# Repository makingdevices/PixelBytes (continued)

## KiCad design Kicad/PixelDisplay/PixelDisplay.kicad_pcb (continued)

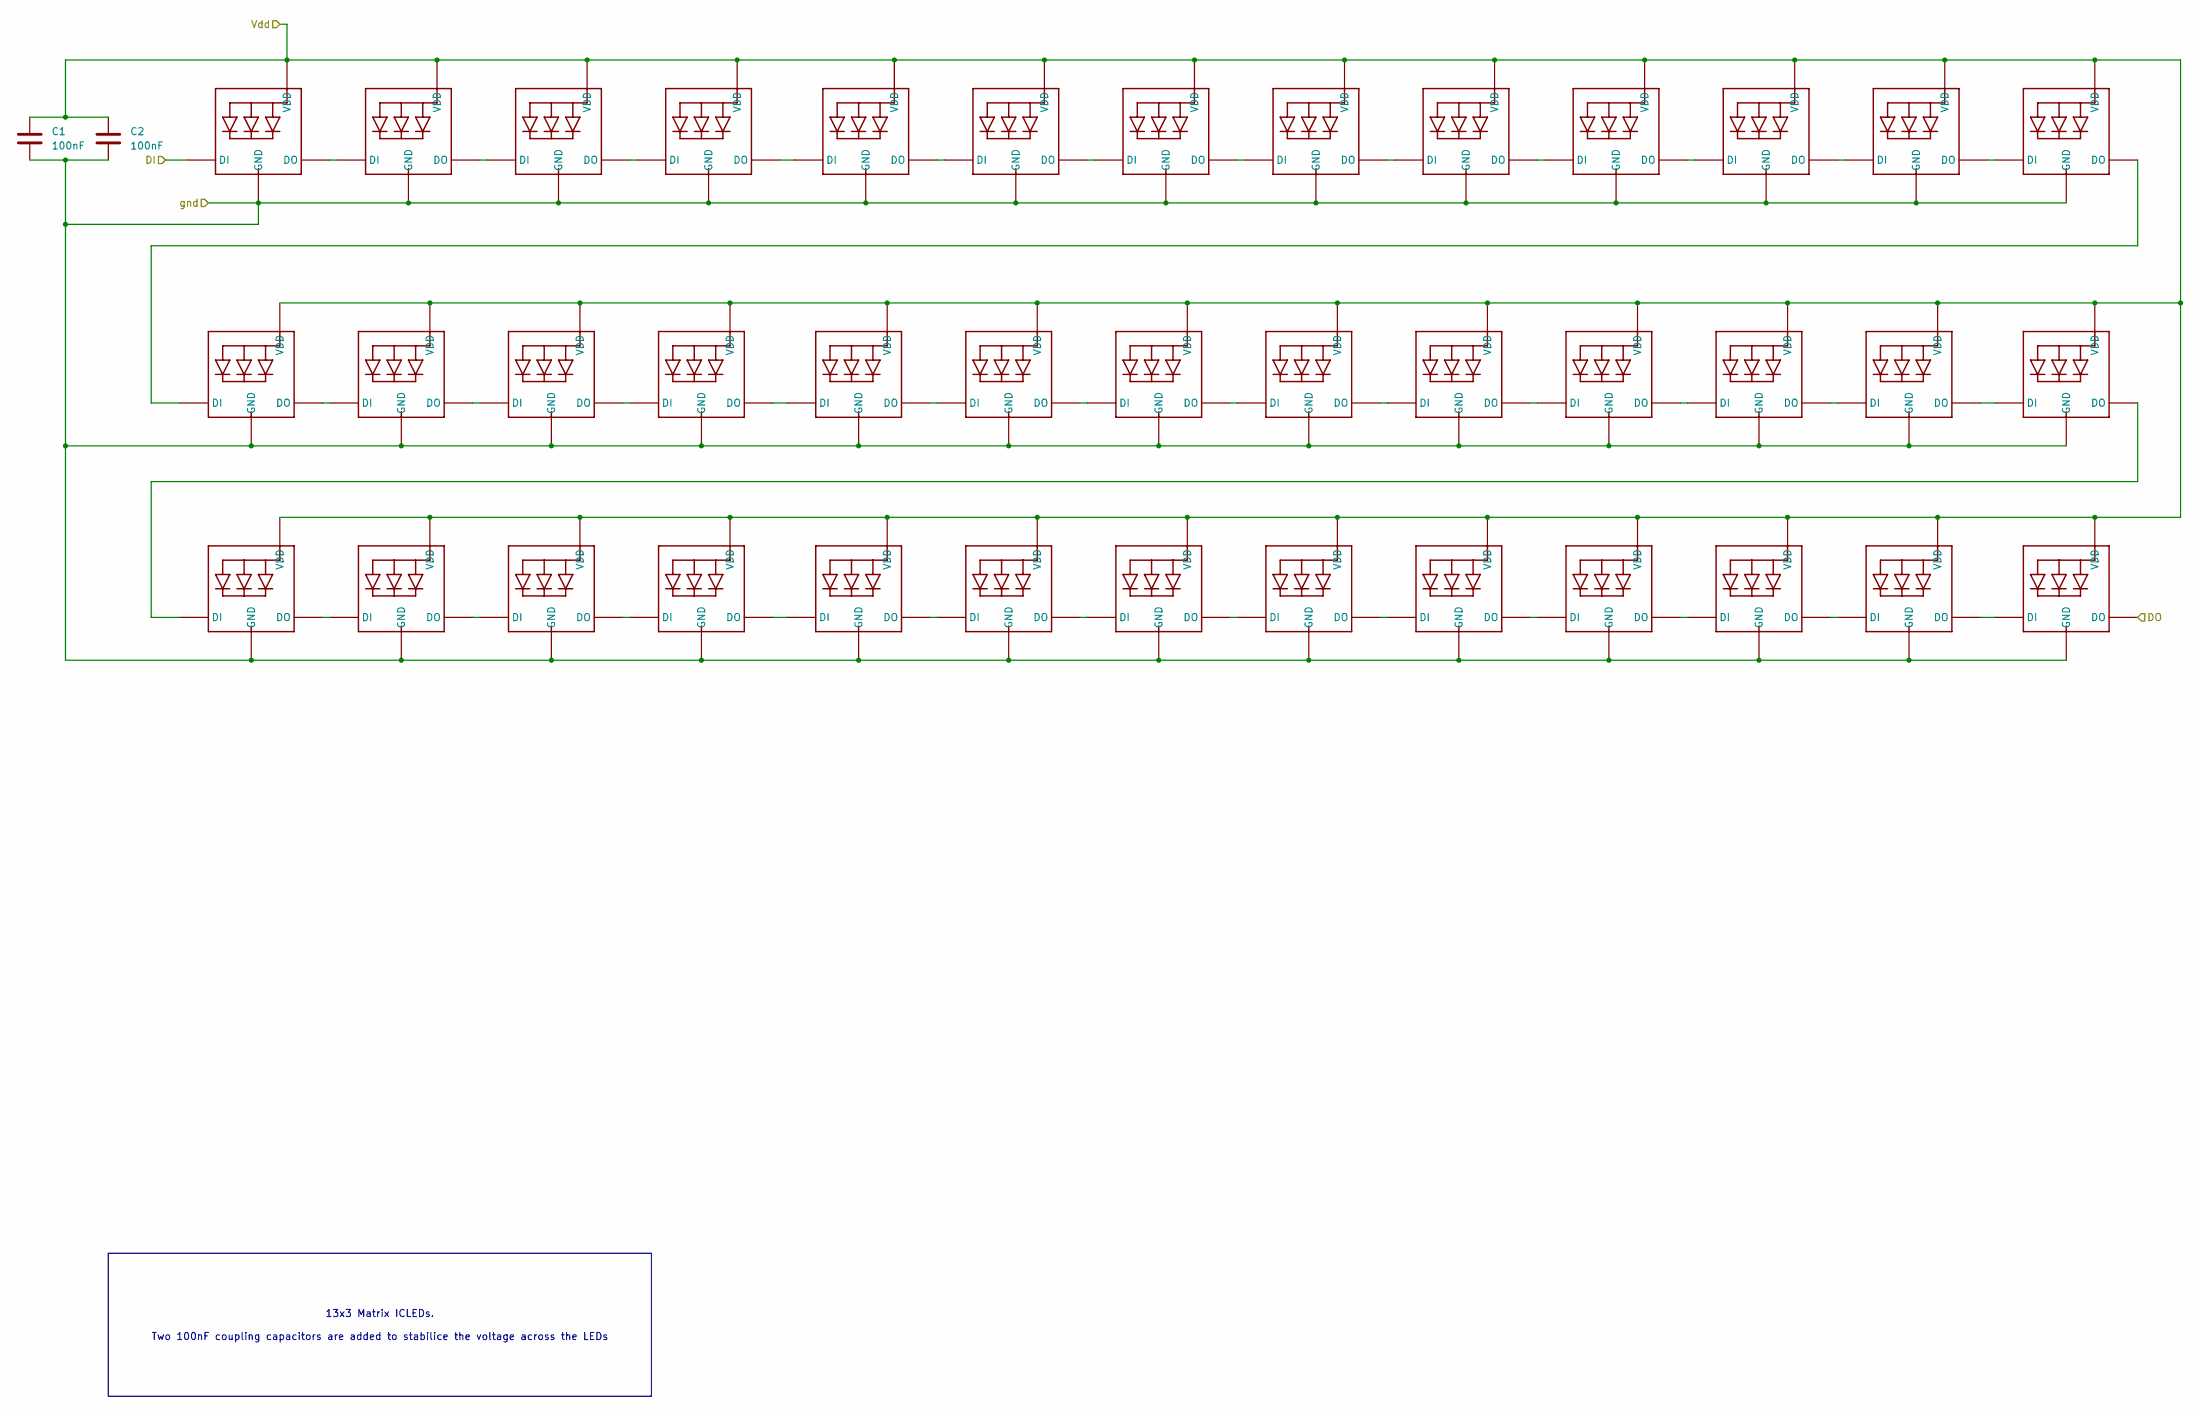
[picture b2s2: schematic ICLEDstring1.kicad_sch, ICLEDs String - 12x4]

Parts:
C1, C2: 100nF; C_0805_2012Metric
ICled1, ICled2, ICled3, ICled4, ICled5, ICled6, ICled7, ICled8, ICled9, ICled10, ICled11, ICled12, ICled13, ICled14, ICled15, ICled16, ICled17, ICled18, ICled19, ICled20, ICled21, ICled22, ICled23, ICled24, ICled25, ICled26, ICled27, ICled28, ICled29, ICled30, ICled31, ICled32, ICled33, ICled34, ICled35, ICled36, ICled37, ICled38, ICled39: 1312020030000

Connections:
unnamed: ICled1.3-DIN (DI), ICled37.1-DOUT (DO)
unnamed: ICled1.1-DOUT (DO), ICled4.3-DIN (DI)
unnamed: ICled2.3-DIN (DI), ICled38.1-DOUT (DO)
unnamed: ICled2.1-DOUT (DO), ICled5.3-DIN (DI)
unnamed: ICled3.1-DOUT (DO), ICled6.3-DIN (DI)
unnamed: ICled4.1-DOUT (DO), ICled7.3-DIN (DI)
unnamed: ICled5.1-DOUT (DO), ICled8.3-DIN (DI)
unnamed: ICled6.1-DOUT (DO), ICled9.3-DIN (DI)
unnamed: ICled7.1-DOUT (DO), ICled10.3-DIN (DI)
unnamed: ICled10.1-DOUT (DO), ICled13.3-DIN (DI)
unnamed: ICled8.1-DOUT (DO), ICled11.3-DIN (DI)
unnamed: ICled11.1-DOUT (DO), ICled14.3-DIN (DI)
unnamed: ICled9.1-DOUT (DO), ICled12.3-DIN (DI)
unnamed: ICled12.1-DOUT (DO), ICled15.3-DIN (DI)
unnamed: ICled13.1-DOUT (DO), ICled16.3-DIN (DI)
unnamed: ICled14.1-DOUT (DO), ICled17.3-DIN (DI)
unnamed: ICled15.1-DOUT (DO), ICled18.3-DIN (DI)
unnamed: ICled16.1-DOUT (DO), ICled19.3-DIN (DI)
unnamed: ICled17.1-DOUT (DO), ICled20.3-DIN (DI)
unnamed: ICled18.1-DOUT (DO), ICled21.3-DIN (DI)
unnamed: ICled19.1-DOUT (DO), ICled22.3-DIN (DI)
unnamed: ICled20.1-DOUT (DO), ICled23.3-DIN (DI)
unnamed: ICled21.1-DOUT (DO), ICled24.3-DIN (DI)
unnamed: ICled22.1-DOUT (DO), ICled25.3-DIN (DI)
unnamed: ICled23.1-DOUT (DO), ICled26.3-DIN (DI)
unnamed: ICled24.1-DOUT (DO), ICled27.3-DIN (DI)
unnamed: ICled25.1-DOUT (DO), ICled28.3-DIN (DI)
unnamed: ICled26.1-DOUT (DO), ICled29.3-DIN (DI)
unnamed: ICled27.1-DOUT (DO), ICled30.3-DIN (DI)
unnamed: ICled28.1-DOUT (DO), ICled31.3-DIN (DI)
unnamed: ICled29.1-DOUT (DO), ICled32.3-DIN (DI)
unnamed: ICled30.1-DOUT (DO), ICled33.3-DIN (DI)
unnamed: ICled31.1-DOUT (DO), ICled34.3-DIN (DI)
unnamed: ICled32.1-DOUT (DO), ICled35.3-DIN (DI)
unnamed: ICled33.1-DOUT (DO), ICled36.3-DIN (DI)
unnamed: ICled34.1-DOUT (DO), ICled38.3-DIN (DI)
unnamed: ICled35.1-DOUT (DO), ICled39.3-DIN (DI)
unnamed: ICled36.1-DOUT (DO), ICled37.3-DIN (DI)
Vdd_str1: C1.1, C2.1, ICled1.2-VDD (VDD), ICled2.2-VDD (VDD), ICled3.2-VDD (VDD), ICled4.2-VDD (VDD), ICled5.2-VDD (VDD), ICled6.2-VDD (VDD), ICled7.2-VDD (VDD), ICled8.2-VDD (VDD), ICled9.2-VDD (VDD), ICled10.2-VDD (VDD), ICled11.2-VDD (VDD), ICled12.2-VDD (VDD), ICled13.2-VDD (VDD), ICled14.2-VDD (VDD), ICled15.2-VDD (VDD), ICled16.2-VDD (VDD), ICled17.2-VDD (VDD), ICled18.2-VDD (VDD), ICled19.2-VDD (VDD), ICled20.2-VDD (VDD), ICled21.2-VDD (VDD), ICled22.2-VDD (VDD), ICled23.2-VDD (VDD), ICled24.2-VDD (VDD), ICled25.2-VDD (VDD), ICled26.2-VDD (VDD), ICled27.2-VDD (VDD), ICled28.2-VDD (VDD), ICled29.2-VDD (VDD), ICled30.2-VDD (VDD), ICled31.2-VDD (VDD), ICled32.2-VDD (VDD), ICled33.2-VDD (VDD), ICled34.2-VDD (VDD), ICled35.2-VDD (VDD), ICled36.2-VDD (VDD), ICled37.2-VDD (VDD), ICled38.2-VDD (VDD), ICled39.2-VDD (VDD); also elsewhere on the board
Vss_str1: C1.2, C2.2, ICled1.4-GND (GND), ICled2.4-GND (GND), ICled3.4-GND (GND), ICled4.4-GND (GND), ICled5.4-GND (GND), ICled6.4-GND (GND), ICled7.4-GND (GND), ICled8.4-GND (GND), ICled9.4-GND (GND), ICled10.4-GND (GND), ICled11.4-GND (GND), ICled12.4-GND (GND), ICled13.4-GND (GND), ICled14.4-GND (GND), ICled15.4-GND (GND), ICled16.4-GND (GND), ICled17.4-GND (GND), ICled18.4-GND (GND), ICled19.4-GND (GND), ICled20.4-GND (GND), ICled21.4-GND (GND), ICled22.4-GND (GND), ICled23.4-GND (GND), ICled24.4-GND (GND), ICled25.4-GND (GND), ICled26.4-GND (GND), ICled27.4-GND (GND), ICled28.4-GND (GND), ICled29.4-GND (GND), ICled30.4-GND (GND), ICled31.4-GND (GND), ICled32.4-GND (GND), ICled33.4-GND (GND), ICled34.4-GND (GND), ICled35.4-GND (GND), ICled36.4-GND (GND), ICled37.4-GND (GND), ICled38.4-GND (GND), ICled39.4-GND (GND); also elsewhere on the board
din_led_pwm_1: ICled3.3-DIN (DI); also elsewhere on the board
dout_led_pwm_1: ICled39.1-DOUT (DO); also elsewhere on the board

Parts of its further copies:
C3, C4, C5, C6, C7, C8, C9, C10, C11, C12: 100nF; C_0805_2012Metric
ICled40, ICled41, ICled42, ICled43, ICled44, ICled45, ICled46, ICled47, ICled48, ICled49, ICled50, ICled51, ICled52, ICled53, ICled54, ICled55, ICled56, ICled57, ICled58, ICled59, ICled60, ICled61, ICled62, ICled63, ICled64, ICled65, ICled66, ICled67, ICled68, ICled69, ICled70, ICled71, ICled72, ICled73, ICled74, ICled75, ICled76, ICled77, ICled78, ICled79, ICled80, ICled81, ICled82, ICled83, ICled84, ICled85, ICled86, ICled87, ICled88, ICled89, ICled90, ICled91, ICled92, ICled93, ICled94, ICled95, ICled96, ICled97, ICled98, ICled99, ICled100, ICled101, ICled102, ICled103, ICled104, ICled105, ICled106, ICled107, ICled108, ICled109, ICled110, ICled111, ICled112, ICled113, ICled114, ICled115, ICled116, ICled117, ICled118, ICled119, ICled120, ICled121, ICled122, ICled123, ICled124, ICled125, ICled126, ICled127, ICled128, ICled129, ICled130, ICled131, ICled132, ICled133, ICled134, ICled135, ICled136, ICled137, ICled138, ICled139, ICled140, ICled141, ICled142, ICled143, ICled144, ICled145, ICled146, ICled147, ICled148, ICled149, ICled150, ICled151, ICled152, ICled153, ICled154, ICled155, ICled156, ICled157, ICled158, ICled159, ICled160, ICled161, ICled162, ICled163, ICled164, ICled165, ICled166, ICled167, ICled168, ICled169, ICled170, ICled171, ICled172, ICled173, ICled174, ICled175, ICled176, ICled177, ICled178, ICled179, ICled180, ICled181, ICled182, ICled183, ICled184, ICled185, ICled186, ICled187, ICled188, ICled189, ICled190, ICled191, ICled192, ICled193, ICled194, ICled195, ICled196, ICled197, ICled198, ICled199, ICled200, ICled201, ICled202, ICled203, ICled204, ICled205, ICled206, ICled207, ICled208, ICled209, ICled210, ICled211, ICled212, ICled213, ICled214, ICled215, ICled216, ICled217, ICled218, ICled219, ICled220, ICled221, ICled222, ICled223, ICled224, ICled225, ICled226, ICled227, ICled228, ICled229, ICled230, ICled231, ICled232, ICled233, ICled234: 1312020030000

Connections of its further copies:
unnamed: ICled40.3-DIN (DI), ICled76.1-DOUT (DO)
unnamed: ICled40.1-DOUT (DO), ICled43.3-DIN (DI)
unnamed: ICled41.3-DIN (DI), ICled77.1-DOUT (DO)
unnamed: ICled41.1-DOUT (DO), ICled44.3-DIN (DI)
unnamed: ICled42.1-DOUT (DO), ICled45.3-DIN (DI)
unnamed: ICled43.1-DOUT (DO), ICled46.3-DIN (DI)
unnamed: ICled44.1-DOUT (DO), ICled47.3-DIN (DI)
unnamed: ICled45.1-DOUT (DO), ICled48.3-DIN (DI)
unnamed: ICled46.1-DOUT (DO), ICled49.3-DIN (DI)
unnamed: ICled47.1-DOUT (DO), ICled50.3-DIN (DI)
unnamed: ICled48.1-DOUT (DO), ICled51.3-DIN (DI)
unnamed: ICled49.1-DOUT (DO), ICled52.3-DIN (DI)
unnamed: ICled50.1-DOUT (DO), ICled53.3-DIN (DI)
unnamed: ICled51.1-DOUT (DO), ICled54.3-DIN (DI)
unnamed: ICled52.1-DOUT (DO), ICled55.3-DIN (DI)
unnamed: ICled53.1-DOUT (DO), ICled56.3-DIN (DI)
unnamed: ICled54.1-DOUT (DO), ICled57.3-DIN (DI)
unnamed: ICled55.1-DOUT (DO), ICled58.3-DIN (DI)
unnamed: ICled56.1-DOUT (DO), ICled59.3-DIN (DI)
unnamed: ICled57.1-DOUT (DO), ICled60.3-DIN (DI)
unnamed: ICled58.1-DOUT (DO), ICled61.3-DIN (DI)
unnamed: ICled59.1-DOUT (DO), ICled62.3-DIN (DI)
unnamed: ICled60.1-DOUT (DO), ICled63.3-DIN (DI)
unnamed: ICled61.1-DOUT (DO), ICled64.3-DIN (DI)
unnamed: ICled62.1-DOUT (DO), ICled65.3-DIN (DI)
unnamed: ICled63.1-DOUT (DO), ICled66.3-DIN (DI)
unnamed: ICled64.1-DOUT (DO), ICled67.3-DIN (DI)
unnamed: ICled65.1-DOUT (DO), ICled68.3-DIN (DI)
unnamed: ICled66.1-DOUT (DO), ICled69.3-DIN (DI)
unnamed: ICled67.1-DOUT (DO), ICled70.3-DIN (DI)
unnamed: ICled68.1-DOUT (DO), ICled71.3-DIN (DI)
unnamed: ICled69.1-DOUT (DO), ICled72.3-DIN (DI)
unnamed: ICled70.1-DOUT (DO), ICled73.3-DIN (DI)
unnamed: ICled71.1-DOUT (DO), ICled74.3-DIN (DI)
unnamed: ICled72.1-DOUT (DO), ICled75.3-DIN (DI)
unnamed: ICled73.1-DOUT (DO), ICled77.3-DIN (DI)
unnamed: ICled74.1-DOUT (DO), ICled78.3-DIN (DI)
unnamed: ICled75.1-DOUT (DO), ICled76.3-DIN (DI)
unnamed: ICled79.1-DOUT (DO), ICled82.3-DIN (DI)
unnamed: ICled80.1-DOUT (DO), ICled83.3-DIN (DI)
unnamed: ICled81.1-DOUT (DO), ICled84.3-DIN (DI)
unnamed: ICled82.1-DOUT (DO), ICled85.3-DIN (DI)
unnamed: ICled83.1-DOUT (DO), ICled86.3-DIN (DI)
unnamed: ICled84.1-DOUT (DO), ICled87.3-DIN (DI)
unnamed: ICled85.1-DOUT (DO), ICled88.3-DIN (DI)
unnamed: ICled86.1-DOUT (DO), ICled89.3-DIN (DI)
unnamed: ICled87.1-DOUT (DO), ICled90.3-DIN (DI)
unnamed: ICled88.1-DOUT (DO), ICled91.3-DIN (DI)
unnamed: ICled89.1-DOUT (DO), ICled92.3-DIN (DI)
unnamed: ICled90.1-DOUT (DO), ICled93.3-DIN (DI)
unnamed: ICled91.1-DOUT (DO), ICled94.3-DIN (DI)
unnamed: ICled92.1-DOUT (DO), ICled95.3-DIN (DI)
unnamed: ICled93.1-DOUT (DO), ICled96.3-DIN (DI)
unnamed: ICled94.1-DOUT (DO), ICled97.3-DIN (DI)
unnamed: ICled95.1-DOUT (DO), ICled98.3-DIN (DI)
unnamed: ICled96.1-DOUT (DO), ICled99.3-DIN (DI)
unnamed: ICled97.1-DOUT (DO), ICled100.3-DIN (DI)
unnamed: ICled100.1-DOUT (DO), ICled103.3-DIN (DI)
unnamed: ICled98.1-DOUT (DO), ICled101.3-DIN (DI)
unnamed: ICled101.1-DOUT (DO), ICled104.3-DIN (DI)
unnamed: ICled99.1-DOUT (DO), ICled102.3-DIN (DI)
unnamed: ICled102.1-DOUT (DO), ICled105.3-DIN (DI)
unnamed: ICled103.1-DOUT (DO), ICled106.3-DIN (DI)
unnamed: ICled104.1-DOUT (DO), ICled107.3-DIN (DI)
unnamed: ICled105.1-DOUT (DO), ICled108.3-DIN (DI)
unnamed: ICled106.1-DOUT (DO), ICled109.3-DIN (DI)
unnamed: ICled107.1-DOUT (DO), ICled110.3-DIN (DI)
unnamed: ICled108.1-DOUT (DO), ICled111.3-DIN (DI)
unnamed: ICled109.1-DOUT (DO), ICled112.3-DIN (DI)
unnamed: ICled110.1-DOUT (DO), ICled113.3-DIN (DI)
unnamed: ICled111.1-DOUT (DO), ICled114.3-DIN (DI)
unnamed: ICled112.1-DOUT (DO), ICled116.3-DIN (DI)
unnamed: ICled113.1-DOUT (DO), ICled117.3-DIN (DI)
unnamed: ICled114.1-DOUT (DO), ICled115.3-DIN (DI)
unnamed: ICled79.3-DIN (DI), ICled115.1-DOUT (DO)
unnamed: ICled80.3-DIN (DI), ICled116.1-DOUT (DO)
unnamed: ICled118.3-DIN (DI), ICled154.1-DOUT (DO)
unnamed: ICled118.1-DOUT (DO), ICled121.3-DIN (DI)
unnamed: ICled119.3-DIN (DI), ICled155.1-DOUT (DO)
unnamed: ICled119.1-DOUT (DO), ICled122.3-DIN (DI)
unnamed: ICled120.1-DOUT (DO), ICled123.3-DIN (DI)
unnamed: ICled121.1-DOUT (DO), ICled124.3-DIN (DI)
unnamed: ICled122.1-DOUT (DO), ICled125.3-DIN (DI)
unnamed: ICled123.1-DOUT (DO), ICled126.3-DIN (DI)
unnamed: ICled124.1-DOUT (DO), ICled127.3-DIN (DI)
unnamed: ICled125.1-DOUT (DO), ICled128.3-DIN (DI)
unnamed: ICled126.1-DOUT (DO), ICled129.3-DIN (DI)
unnamed: ICled127.1-DOUT (DO), ICled130.3-DIN (DI)
unnamed: ICled128.1-DOUT (DO), ICled131.3-DIN (DI)
unnamed: ICled129.1-DOUT (DO), ICled132.3-DIN (DI)
unnamed: ICled130.1-DOUT (DO), ICled133.3-DIN (DI)
unnamed: ICled131.1-DOUT (DO), ICled134.3-DIN (DI)
unnamed: ICled132.1-DOUT (DO), ICled135.3-DIN (DI)
unnamed: ICled133.1-DOUT (DO), ICled136.3-DIN (DI)
unnamed: ICled134.1-DOUT (DO), ICled137.3-DIN (DI)
unnamed: ICled135.1-DOUT (DO), ICled138.3-DIN (DI)
unnamed: ICled136.1-DOUT (DO), ICled139.3-DIN (DI)
unnamed: ICled137.1-DOUT (DO), ICled140.3-DIN (DI)
unnamed: ICled138.1-DOUT (DO), ICled141.3-DIN (DI)
unnamed: ICled139.1-DOUT (DO), ICled142.3-DIN (DI)
unnamed: ICled140.1-DOUT (DO), ICled143.3-DIN (DI)
unnamed: ICled141.1-DOUT (DO), ICled144.3-DIN (DI)
unnamed: ICled142.1-DOUT (DO), ICled145.3-DIN (DI)
unnamed: ICled143.1-DOUT (DO), ICled146.3-DIN (DI)
unnamed: ICled144.1-DOUT (DO), ICled147.3-DIN (DI)
unnamed: ICled145.1-DOUT (DO), ICled148.3-DIN (DI)
unnamed: ICled146.1-DOUT (DO), ICled149.3-DIN (DI)
unnamed: ICled147.1-DOUT (DO), ICled150.3-DIN (DI)
unnamed: ICled148.1-DOUT (DO), ICled151.3-DIN (DI)
unnamed: ICled149.1-DOUT (DO), ICled152.3-DIN (DI)
unnamed: ICled150.1-DOUT (DO), ICled153.3-DIN (DI)
unnamed: ICled151.1-DOUT (DO), ICled155.3-DIN (DI)
unnamed: ICled152.1-DOUT (DO), ICled156.3-DIN (DI)
unnamed: ICled153.1-DOUT (DO), ICled154.3-DIN (DI)
unnamed: ICled157.3-DIN (DI), ICled193.1-DOUT (DO)
unnamed: ICled157.1-DOUT (DO), ICled160.3-DIN (DI)
unnamed: ICled158.3-DIN (DI), ICled194.1-DOUT (DO)
unnamed: ICled158.1-DOUT (DO), ICled161.3-DIN (DI)
unnamed: ICled159.1-DOUT (DO), ICled162.3-DIN (DI)
unnamed: ICled160.1-DOUT (DO), ICled163.3-DIN (DI)
unnamed: ICled161.1-DOUT (DO), ICled164.3-DIN (DI)
unnamed: ICled162.1-DOUT (DO), ICled165.3-DIN (DI)
unnamed: ICled163.1-DOUT (DO), ICled166.3-DIN (DI)
unnamed: ICled164.1-DOUT (DO), ICled167.3-DIN (DI)
unnamed: ICled165.1-DOUT (DO), ICled168.3-DIN (DI)
unnamed: ICled166.1-DOUT (DO), ICled169.3-DIN (DI)
unnamed: ICled167.1-DOUT (DO), ICled170.3-DIN (DI)
unnamed: ICled168.1-DOUT (DO), ICled171.3-DIN (DI)
unnamed: ICled169.1-DOUT (DO), ICled172.3-DIN (DI)
unnamed: ICled170.1-DOUT (DO), ICled173.3-DIN (DI)
unnamed: ICled171.1-DOUT (DO), ICled174.3-DIN (DI)
unnamed: ICled172.1-DOUT (DO), ICled175.3-DIN (DI)
unnamed: ICled173.1-DOUT (DO), ICled176.3-DIN (DI)
unnamed: ICled174.1-DOUT (DO), ICled177.3-DIN (DI)
unnamed: ICled175.1-DOUT (DO), ICled178.3-DIN (DI)
unnamed: ICled176.1-DOUT (DO), ICled179.3-DIN (DI)
unnamed: ICled177.1-DOUT (DO), ICled180.3-DIN (DI)
unnamed: ICled178.1-DOUT (DO), ICled181.3-DIN (DI)
unnamed: ICled179.1-DOUT (DO), ICled182.3-DIN (DI)
unnamed: ICled180.1-DOUT (DO), ICled183.3-DIN (DI)
unnamed: ICled181.1-DOUT (DO), ICled184.3-DIN (DI)
unnamed: ICled182.1-DOUT (DO), ICled185.3-DIN (DI)
unnamed: ICled183.1-DOUT (DO), ICled186.3-DIN (DI)
unnamed: ICled184.1-DOUT (DO), ICled187.3-DIN (DI)
unnamed: ICled185.1-DOUT (DO), ICled188.3-DIN (DI)
unnamed: ICled186.1-DOUT (DO), ICled189.3-DIN (DI)
unnamed: ICled187.1-DOUT (DO), ICled190.3-DIN (DI)
unnamed: ICled188.1-DOUT (DO), ICled191.3-DIN (DI)
unnamed: ICled189.1-DOUT (DO), ICled192.3-DIN (DI)
unnamed: ICled190.1-DOUT (DO), ICled194.3-DIN (DI)
unnamed: ICled191.1-DOUT (DO), ICled195.3-DIN (DI)
unnamed: ICled192.1-DOUT (DO), ICled193.3-DIN (DI)
unnamed: ICled196.3-DIN (DI), ICled232.1-DOUT (DO)
unnamed: ICled196.1-DOUT (DO), ICled199.3-DIN (DI)
unnamed: ICled197.3-DIN (DI), ICled233.1-DOUT (DO)
unnamed: ICled197.1-DOUT (DO), ICled200.3-DIN (DI)
unnamed: ICled198.1-DOUT (DO), ICled201.3-DIN (DI)
unnamed: ICled199.1-DOUT (DO), ICled202.3-DIN (DI)
unnamed: ICled200.1-DOUT (DO), ICled203.3-DIN (DI)
unnamed: ICled201.1-DOUT (DO), ICled204.3-DIN (DI)
unnamed: ICled202.1-DOUT (DO), ICled205.3-DIN (DI)
unnamed: ICled203.1-DOUT (DO), ICled206.3-DIN (DI)
unnamed: ICled204.1-DOUT (DO), ICled207.3-DIN (DI)
unnamed: ICled205.1-DOUT (DO), ICled208.3-DIN (DI)
unnamed: ICled206.1-DOUT (DO), ICled209.3-DIN (DI)
unnamed: ICled207.1-DOUT (DO), ICled210.3-DIN (DI)
unnamed: ICled208.1-DOUT (DO), ICled211.3-DIN (DI)
unnamed: ICled209.1-DOUT (DO), ICled212.3-DIN (DI)
unnamed: ICled210.1-DOUT (DO), ICled213.3-DIN (DI)
unnamed: ICled211.1-DOUT (DO), ICled214.3-DIN (DI)
unnamed: ICled212.1-DOUT (DO), ICled215.3-DIN (DI)
unnamed: ICled213.1-DOUT (DO), ICled216.3-DIN (DI)
unnamed: ICled214.1-DOUT (DO), ICled217.3-DIN (DI)
unnamed: ICled215.1-DOUT (DO), ICled218.3-DIN (DI)
unnamed: ICled216.1-DOUT (DO), ICled219.3-DIN (DI)
unnamed: ICled217.1-DOUT (DO), ICled220.3-DIN (DI)
unnamed: ICled218.1-DOUT (DO), ICled221.3-DIN (DI)
unnamed: ICled219.1-DOUT (DO), ICled222.3-DIN (DI)
unnamed: ICled220.1-DOUT (DO), ICled223.3-DIN (DI)
unnamed: ICled221.1-DOUT (DO), ICled224.3-DIN (DI)
unnamed: ICled222.1-DOUT (DO), ICled225.3-DIN (DI)
unnamed: ICled223.1-DOUT (DO), ICled226.3-DIN (DI)
unnamed: ICled224.1-DOUT (DO), ICled227.3-DIN (DI)
unnamed: ICled225.1-DOUT (DO), ICled228.3-DIN (DI)
unnamed: ICled226.1-DOUT (DO), ICled229.3-DIN (DI)
unnamed: ICled227.1-DOUT (DO), ICled230.3-DIN (DI)
unnamed: ICled228.1-DOUT (DO), ICled231.3-DIN (DI)
unnamed: ICled229.1-DOUT (DO), ICled233.3-DIN (DI)
unnamed: ICled230.1-DOUT (DO), ICled234.3-DIN (DI)
unnamed: ICled231.1-DOUT (DO), ICled232.3-DIN (DI)
Vdd_str2: C3.1, C4.1, ICled40.2-VDD (VDD), ICled41.2-VDD (VDD), ICled42.2-VDD (VDD), ICled43.2-VDD (VDD), ICled44.2-VDD (VDD), ICled45.2-VDD (VDD), ICled46.2-VDD (VDD), ICled47.2-VDD (VDD), ICled48.2-VDD (VDD), ICled49.2-VDD (VDD), ICled50.2-VDD (VDD), ICled51.2-VDD (VDD), ICled52.2-VDD (VDD), ICled53.2-VDD (VDD), ICled54.2-VDD (VDD), ICled55.2-VDD (VDD), ICled56.2-VDD (VDD), ICled57.2-VDD (VDD), ICled58.2-VDD (VDD), ICled59.2-VDD (VDD), ICled60.2-VDD (VDD), ICled61.2-VDD (VDD), ICled62.2-VDD (VDD), ICled63.2-VDD (VDD), ICled64.2-VDD (VDD), ICled65.2-VDD (VDD), ICled66.2-VDD (VDD), ICled67.2-VDD (VDD), ICled68.2-VDD (VDD), ICled69.2-VDD (VDD), ICled70.2-VDD (VDD), ICled71.2-VDD (VDD), ICled72.2-VDD (VDD), ICled73.2-VDD (VDD), ICled74.2-VDD (VDD), ICled75.2-VDD (VDD), ICled76.2-VDD (VDD), ICled77.2-VDD (VDD), ICled78.2-VDD (VDD); also elsewhere on the board
Vdd_str3: C5.1, C6.1, ICled79.2-VDD (VDD), ICled80.2-VDD (VDD), ICled81.2-VDD (VDD), ICled82.2-VDD (VDD), ICled83.2-VDD (VDD), ICled84.2-VDD (VDD), ICled85.2-VDD (VDD), ICled86.2-VDD (VDD), ICled87.2-VDD (VDD), ICled88.2-VDD (VDD), ICled89.2-VDD (VDD), ICled90.2-VDD (VDD), ICled91.2-VDD (VDD), ICled92.2-VDD (VDD), ICled93.2-VDD (VDD), ICled94.2-VDD (VDD), ICled95.2-VDD (VDD), ICled96.2-VDD (VDD), ICled97.2-VDD (VDD), ICled98.2-VDD (VDD), ICled99.2-VDD (VDD), ICled100.2-VDD (VDD), ICled101.2-VDD (VDD), ICled102.2-VDD (VDD), ICled103.2-VDD (VDD), ICled104.2-VDD (VDD), ICled105.2-VDD (VDD), ICled106.2-VDD (VDD), ICled107.2-VDD (VDD), ICled108.2-VDD (VDD), ICled109.2-VDD (VDD), ICled110.2-VDD (VDD), ICled111.2-VDD (VDD), ICled112.2-VDD (VDD), ICled113.2-VDD (VDD), ICled114.2-VDD (VDD), ICled115.2-VDD (VDD), ICled116.2-VDD (VDD), ICled117.2-VDD (VDD); also elsewhere on the board
Vdd_str4: C7.1, C8.1, ICled118.2-VDD (VDD), ICled119.2-VDD (VDD), ICled120.2-VDD (VDD), ICled121.2-VDD (VDD), ICled122.2-VDD (VDD), ICled123.2-VDD (VDD), ICled124.2-VDD (VDD), ICled125.2-VDD (VDD), ICled126.2-VDD (VDD), ICled127.2-VDD (VDD), ICled128.2-VDD (VDD), ICled129.2-VDD (VDD), ICled130.2-VDD (VDD), ICled131.2-VDD (VDD), ICled132.2-VDD (VDD), ICled133.2-VDD (VDD), ICled134.2-VDD (VDD), ICled135.2-VDD (VDD), ICled136.2-VDD (VDD), ICled137.2-VDD (VDD), ICled138.2-VDD (VDD), ICled139.2-VDD (VDD), ICled140.2-VDD (VDD), ICled141.2-VDD (VDD), ICled142.2-VDD (VDD), ICled143.2-VDD (VDD), ICled144.2-VDD (VDD), ICled145.2-VDD (VDD), ICled146.2-VDD (VDD), ICled147.2-VDD (VDD), ICled148.2-VDD (VDD), ICled149.2-VDD (VDD), ICled150.2-VDD (VDD), ICled151.2-VDD (VDD), ICled152.2-VDD (VDD), ICled153.2-VDD (VDD), ICled154.2-VDD (VDD), ICled155.2-VDD (VDD), ICled156.2-VDD (VDD); also elsewhere on the board
Vdd_str5: C9.1, C10.1, ICled157.2-VDD (VDD), ICled158.2-VDD (VDD), ICled159.2-VDD (VDD), ICled160.2-VDD (VDD), ICled161.2-VDD (VDD), ICled162.2-VDD (VDD), ICled163.2-VDD (VDD), ICled164.2-VDD (VDD), ICled165.2-VDD (VDD), ICled166.2-VDD (VDD), ICled167.2-VDD (VDD), ICled168.2-VDD (VDD), ICled169.2-VDD (VDD), ICled170.2-VDD (VDD), ICled171.2-VDD (VDD), ICled172.2-VDD (VDD), ICled173.2-VDD (VDD), ICled174.2-VDD (VDD), ICled175.2-VDD (VDD), ICled176.2-VDD (VDD), ICled177.2-VDD (VDD), ICled178.2-VDD (VDD), ICled179.2-VDD (VDD), ICled180.2-VDD (VDD), ICled181.2-VDD (VDD), ICled182.2-VDD (VDD), ICled183.2-VDD (VDD), ICled184.2-VDD (VDD), ICled185.2-VDD (VDD), ICled186.2-VDD (VDD), ICled187.2-VDD (VDD), ICled188.2-VDD (VDD), ICled189.2-VDD (VDD), ICled190.2-VDD (VDD), ICled191.2-VDD (VDD), ICled192.2-VDD (VDD), ICled193.2-VDD (VDD), ICled194.2-VDD (VDD), ICled195.2-VDD (VDD); also elsewhere on the board
Vdd_str6: C11.1, C12.1, ICled196.2-VDD (VDD), ICled197.2-VDD (VDD), ICled198.2-VDD (VDD), ICled199.2-VDD (VDD), ICled200.2-VDD (VDD), ICled201.2-VDD (VDD), ICled202.2-VDD (VDD), ICled203.2-VDD (VDD), ICled204.2-VDD (VDD), ICled205.2-VDD (VDD), ICled206.2-VDD (VDD), ICled207.2-VDD (VDD), ICled208.2-VDD (VDD), ICled209.2-VDD (VDD), ICled210.2-VDD (VDD), ICled211.2-VDD (VDD), ICled212.2-VDD (VDD), ICled213.2-VDD (VDD), ICled214.2-VDD (VDD), ICled215.2-VDD (VDD), ICled216.2-VDD (VDD), ICled217.2-VDD (VDD), ICled218.2-VDD (VDD), ICled219.2-VDD (VDD), ICled220.2-VDD (VDD), ICled221.2-VDD (VDD), ICled222.2-VDD (VDD), ICled223.2-VDD (VDD), ICled224.2-VDD (VDD), ICled225.2-VDD (VDD), ICled226.2-VDD (VDD), ICled227.2-VDD (VDD), ICled228.2-VDD (VDD), ICled229.2-VDD (VDD), ICled230.2-VDD (VDD), ICled231.2-VDD (VDD), ICled232.2-VDD (VDD), ICled233.2-VDD (VDD), ICled234.2-VDD (VDD); also elsewhere on the board
Vss_str2: C3.2, C4.2, ICled40.4-GND (GND), ICled41.4-GND (GND), ICled42.4-GND (GND), ICled43.4-GND (GND), ICled44.4-GND (GND), ICled45.4-GND (GND), ICled46.4-GND (GND), ICled47.4-GND (GND), ICled48.4-GND (GND), ICled49.4-GND (GND), ICled50.4-GND (GND), ICled51.4-GND (GND), ICled52.4-GND (GND), ICled53.4-GND (GND), ICled54.4-GND (GND), ICled55.4-GND (GND), ICled56.4-GND (GND), ICled57.4-GND (GND), ICled58.4-GND (GND), ICled59.4-GND (GND), ICled60.4-GND (GND), ICled61.4-GND (GND), ICled62.4-GND (GND), ICled63.4-GND (GND), ICled64.4-GND (GND), ICled65.4-GND (GND), ICled66.4-GND (GND), ICled67.4-GND (GND), ICled68.4-GND (GND), ICled69.4-GND (GND), ICled70.4-GND (GND), ICled71.4-GND (GND), ICled72.4-GND (GND), ICled73.4-GND (GND), ICled74.4-GND (GND), ICled75.4-GND (GND), ICled76.4-GND (GND), ICled77.4-GND (GND), ICled78.4-GND (GND); also elsewhere on the board
Vss_str3: C5.2, C6.2, ICled79.4-GND (GND), ICled80.4-GND (GND), ICled81.4-GND (GND), ICled82.4-GND (GND), ICled83.4-GND (GND), ICled84.4-GND (GND), ICled85.4-GND (GND), ICled86.4-GND (GND), ICled87.4-GND (GND), ICled88.4-GND (GND), ICled89.4-GND (GND), ICled90.4-GND (GND), ICled91.4-GND (GND), ICled92.4-GND (GND), ICled93.4-GND (GND), ICled94.4-GND (GND), ICled95.4-GND (GND), ICled96.4-GND (GND), ICled97.4-GND (GND), ICled98.4-GND (GND), ICled99.4-GND (GND), ICled100.4-GND (GND), ICled101.4-GND (GND), ICled102.4-GND (GND), ICled103.4-GND (GND), ICled104.4-GND (GND), ICled105.4-GND (GND), ICled106.4-GND (GND), ICled107.4-GND (GND), ICled108.4-GND (GND), ICled109.4-GND (GND), ICled110.4-GND (GND), ICled111.4-GND (GND), ICled112.4-GND (GND), ICled113.4-GND (GND), ICled114.4-GND (GND), ICled115.4-GND (GND), ICled116.4-GND (GND), ICled117.4-GND (GND); also elsewhere on the board
Vss_str4: C7.2, C8.2, ICled118.4-GND (GND), ICled119.4-GND (GND), ICled120.4-GND (GND), ICled121.4-GND (GND), ICled122.4-GND (GND), ICled123.4-GND (GND), ICled124.4-GND (GND), ICled125.4-GND (GND), ICled126.4-GND (GND), ICled127.4-GND (GND), ICled128.4-GND (GND), ICled129.4-GND (GND), ICled130.4-GND (GND), ICled131.4-GND (GND), ICled132.4-GND (GND), ICled133.4-GND (GND), ICled134.4-GND (GND), ICled135.4-GND (GND), ICled136.4-GND (GND), ICled137.4-GND (GND), ICled138.4-GND (GND), ICled139.4-GND (GND), ICled140.4-GND (GND), ICled141.4-GND (GND), ICled142.4-GND (GND), ICled143.4-GND (GND), ICled144.4-GND (GND), ICled145.4-GND (GND), ICled146.4-GND (GND), ICled147.4-GND (GND), ICled148.4-GND (GND), ICled149.4-GND (GND), ICled150.4-GND (GND), ICled151.4-GND (GND), ICled152.4-GND (GND), ICled153.4-GND (GND), ICled154.4-GND (GND), ICled155.4-GND (GND), ICled156.4-GND (GND); also elsewhere on the board
Vss_str5: C9.2, C10.2, ICled157.4-GND (GND), ICled158.4-GND (GND), ICled159.4-GND (GND), ICled160.4-GND (GND), ICled161.4-GND (GND), ICled162.4-GND (GND), ICled163.4-GND (GND), ICled164.4-GND (GND), ICled165.4-GND (GND), ICled166.4-GND (GND), ICled167.4-GND (GND), ICled168.4-GND (GND), ICled169.4-GND (GND), ICled170.4-GND (GND), ICled171.4-GND (GND), ICled172.4-GND (GND), ICled173.4-GND (GND), ICled174.4-GND (GND), ICled175.4-GND (GND), ICled176.4-GND (GND), ICled177.4-GND (GND), ICled178.4-GND (GND), ICled179.4-GND (GND), ICled180.4-GND (GND), ICled181.4-GND (GND), ICled182.4-GND (GND), ICled183.4-GND (GND), ICled184.4-GND (GND), ICled185.4-GND (GND), ICled186.4-GND (GND), ICled187.4-GND (GND), ICled188.4-GND (GND), ICled189.4-GND (GND), ICled190.4-GND (GND), ICled191.4-GND (GND), ICled192.4-GND (GND), ICled193.4-GND (GND), ICled194.4-GND (GND), ICled195.4-GND (GND); also elsewhere on the board
Vss_str6: C11.2, C12.2, ICled196.4-GND (GND), ICled197.4-GND (GND), ICled198.4-GND (GND), ICled199.4-GND (GND), ICled200.4-GND (GND), ICled201.4-GND (GND), ICled202.4-GND (GND), ICled203.4-GND (GND), ICled204.4-GND (GND), ICled205.4-GND (GND), ICled206.4-GND (GND), ICled207.4-GND (GND), ICled208.4-GND (GND), ICled209.4-GND (GND), ICled210.4-GND (GND), ICled211.4-GND (GND), ICled212.4-GND (GND), ICled213.4-GND (GND), ICled214.4-GND (GND), ICled215.4-GND (GND), ICled216.4-GND (GND), ICled217.4-GND (GND), ICled218.4-GND (GND), ICled219.4-GND (GND), ICled220.4-GND (GND), ICled221.4-GND (GND), ICled222.4-GND (GND), ICled223.4-GND (GND), ICled224.4-GND (GND), ICled225.4-GND (GND), ICled226.4-GND (GND), ICled227.4-GND (GND), ICled228.4-GND (GND), ICled229.4-GND (GND), ICled230.4-GND (GND), ICled231.4-GND (GND), ICled232.4-GND (GND), ICled233.4-GND (GND), ICled234.4-GND (GND); also elsewhere on the board
din_led_pwm_2: ICled42.3-DIN (DI); also elsewhere on the board
din_led_pwm_3: ICled81.3-DIN (DI); also elsewhere on the board
din_led_pwm_4: ICled120.3-DIN (DI); also elsewhere on the board
din_led_pwm_5: ICled159.3-DIN (DI); also elsewhere on the board
din_led_pwm_6: ICled198.3-DIN (DI); also elsewhere on the board
dout_led_pwm_2: ICled78.1-DOUT (DO); also elsewhere on the board
dout_led_pwm_3: ICled117.1-DOUT (DO); also elsewhere on the board
dout_led_pwm_4: ICled156.1-DOUT (DO); also elsewhere on the board
dout_led_pwm_5: ICled195.1-DOUT (DO); also elsewhere on the board
dout_led_pwm_6: ICled234.1-DOUT (DO); also elsewhere on the board

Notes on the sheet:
13x3 Matrix ICLEDs. Two 100nF coupling capacitors are added to stabilice the voltage across the LEDs

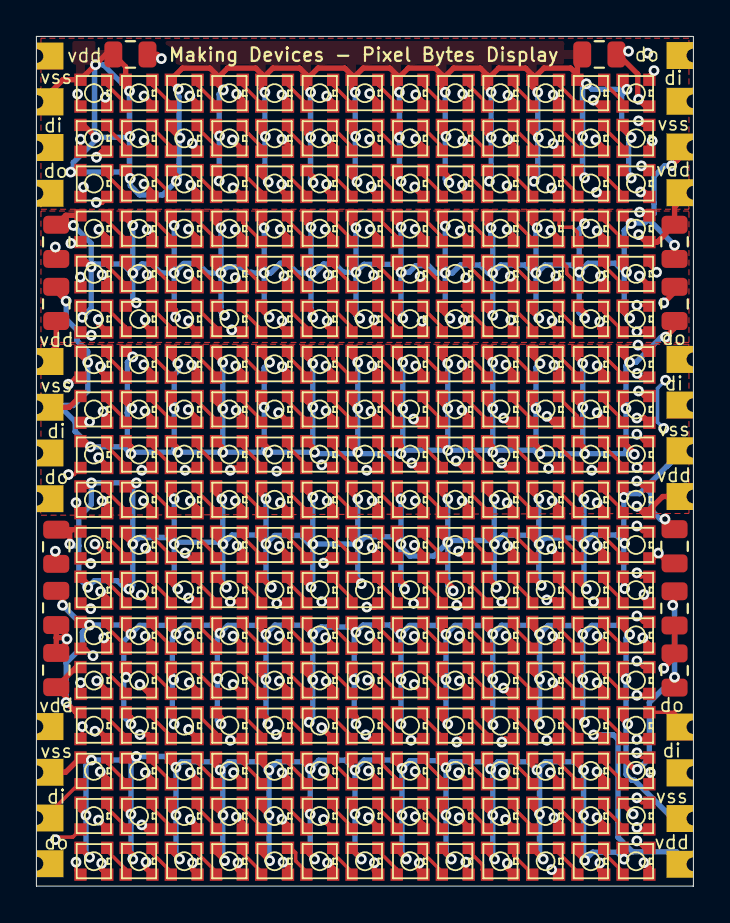
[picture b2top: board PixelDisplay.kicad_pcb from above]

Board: 4 copper layers, 36.5 x 47.2 mm, 252 parts (0 on the bottom side), 252 nets.

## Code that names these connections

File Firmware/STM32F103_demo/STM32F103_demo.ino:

#include "WSEN_ISDS.h"

Sensor_ISDS sensor;
int status;

#include <Adafruit_NeoPixel.h>
#ifdef __AVR__
 #include <avr/power.h> // Required for 16 MHz Adafruit Trinket
#endif

// Which pin on the Arduino is connected to the NeoPixels?
#define PIN PA6 // On Trinket or Gemma, suggest changing this to 1

// How many NeoPixels are attached to the Arduino?
#define NUMPIXELS 234 // Popular NeoPixel ring size
#define DELAYVAL 1 // Time (in milliseconds) to pause between pixels

// When setting up the NeoPixel library, we tell it how many pixels,
// and which pin to use to send signals. Note that for older NeoPixel
// strips you might need to change the third parameter -- see the
// strandtest example for more information on possible values.
Adafruit_NeoPixel pixels(NUMPIXELS, PIN, NEO_GRB + NEO_KHZ800);

int buttonState_up = 0;
int buttonState_down = 0;
int buttonState_left = 0;
int buttonState_right = 0;
int buttonState_b = 0;
int buttonState_a = 0;
int sensorValue = 0;
float batValue = 0;


void read_buttons() {
  buttonState_up = digitalRead(PA0);
  buttonState_down = digitalRead(PA1);
  buttonState_right = digitalRead(PA2);
  buttonState_left = digitalRead(PA3);
  buttonState_a = digitalRead(PA4);
  buttonState_b = digitalRead(PA5);
  if(buttonState_up == LOW){
    digitalWrite(PB14, HIGH);
    Serial.println("Up button pressed!");
  } 
  if(buttonState_down == LOW){
    digitalWrite(PB14, HIGH);
    Serial.println("Down button pressed!");
  } 
  if(buttonState_left == LOW){
    digitalWrite(PB14, HIGH);
    Serial.println("Left button pressed!");
  } 
  if(buttonState_right == LOW){
    digitalWrite(PB14, HIGH);
    Serial.println("Right button pressed!");
  } 
  if(buttonState_b == LOW){
    digitalWrite(PB8, HIGH);
    Serial.println("B button pressed!");
  } 
  if(buttonState_a == LOW){
    digitalWrite(PB8, LOW);
    Serial.println("A button pressed!");
  } 
}

void setup() {
  Serial.begin(9600);
  pixels.begin(); // INITIALIZE NeoPixel strip object (REQUIRED)

  // initialize digital pin LED_BUILTIN as an output.
  pinMode(PA0, INPUT); // UP button
  pinMode(PA1, INPUT); // Down button
  pinMode(PA2, INPUT); // Right button
  pinMode(PA3, INPUT); // Left button
  pinMode(PA4, INPUT); // A button
  pinMode(PA5, INPUT); // B button
  pinMode(PA9, OUTPUT); // B button
  pinMode(PB14, OUTPUT);  // Buzzer enable pin
  pinMode(PB3, OUTPUT);  //Battery measurement enable
  pinMode(PB8, OUTPUT);  //Battery measurement enable
  digitalWrite(PB8, LOW);
  
    // Initialize the I2C interface
  sensor.init(ISDS_ADDRESS_I2C_1);

  // Reset sensor
  status = sensor.SW_RESET();
  if (WE_FAIL == status)
  {
    Serial.println("Error:  SW_RESET(). Stop!");
    while(1);  
  }

  // Set FIFO ODR to 26Hz
  status = sensor.select_ODR(2);
  if (WE_FAIL == status)
    {
    Serial.println("Error:  select_ODR(). Stop!");
    while(1);  
  }

  // Set high performance mode
  status = sensor.set_Mode(2);
  if (WE_FAIL == status)
  {
    Serial.println("Error:  set_Mode(). Stop!");
    while(1);  
  }
  
  Serial.println("Hello there?");

}
// the loop function runs over and over again forever
void loop() {
  int16_t acc_X;
  int16_t acc_Y;
  int16_t acc_Z;
  digitalWrite(PB3, HIGH);  //Connecting bat reading.;
  digitalWrite(PA9, !digitalRead(PA9));  //Toggle led life
  // Get acceleration sensor to measure.
  status = sensor.is_ACC_Ready_To_Read();
  if (WE_FAIL == status)
  {
    Serial.println("Error: is_ACC_Ready_To_Read(). Stop!");
    while(1);
  } 
  // Get acceleration along axis in mg
  status = sensor.get_accelerations(&acc_X,&acc_Y,&acc_Z);
  Serial.println("Acceleration along X,Y,Z axis in [mg]: ");
  Serial.print(acc_X);
  Serial.print(" ");
  Serial.print(acc_Y);
  Serial.print(" ");
  Serial.print(acc_Z);
  Serial.println(" ");
    // Check if sensor is ready to measure the temperature
  status = sensor.is_Temp_Ready();
    
  if (WE_FAIL == status)
  {
    Serial.println("Error: is_Temp_Ready(). Stop!");
    while(1);
  }
  else if (1 == status)
  {
    //Print the temperature on the serial monitor
    
    float temperature;
    if (WE_FAIL == sensor.get_temperature(&temperature))
      {
    Serial.println("Error:  get_temperature(). Stop!");
    while(1);  
    }
    Serial.println("Temperature in [°C]: ");
    Serial.println(temperature);
  }
  for(int i = 0; i<NUMPIXELS; i++){
    pixels.setPixelColor(i, pixels.Color(0, 0, 15));
    read_buttons();
    pixels.show();   // Send the updated pixel colors to the hardware.
  }
  digitalWrite(PB14, LOW);
  for(int i = 0; i<NUMPIXELS; i++){
    pixels.setPixelColor(i, pixels.Color(0, 15, 0));
    read_buttons();
    pixels.show();   // Send the updated pixel colors to the hardware.
  }
  digitalWrite(PB14, LOW);
  for(int i = 0; i<NUMPIXELS; i++){
    pixels.setPixelColor(i, pixels.Color(15,0, 0));
    read_buttons();
    pixels.show();   // Send the updated pixel colors to the hardware.
  }
  digitalWrite(PB14, LOW);

  sensorValue = analogRead(PB0);
  batValue = 0.006445*sensorValue;  // (3.3/1024)*2 -> Vref/resolution * VoltDivider * measurement
  Serial.println("Voltage of the battery: [V]: ");
  Serial.print(batValue);
  Serial.println(" ");

  digitalWrite(PB3, LOW);  //turn off battery reading
  delay(220); 
}

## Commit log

2024-06-20 Preliminar Bill Of Materials
2024-06-20 First project and library for the ICleds
2024-06-24 First V0.1 version. Ordering the PCB to @PCBWAY in a couple of days
2024-09-05 no message
2024-09-22 New version of PixelBytesHost
2024-09-22 New intro for github
2024-09-22 Testing new page
2024-09-26 New firmware for the board
2024-10-16 Demo binary for the board
2024-11-07 Subimos todos los archivos de la v0.25
2024-12-04 Host HW 1.0 finished
2025-02-20 New Version PixelBytesHost
2025-03-25 New Firmware
